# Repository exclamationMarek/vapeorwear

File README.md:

# VAPEorWEAR
Wearable SAO power pack

Designed around a battery, that is upcycled from a single use vape, that a friend of mine found (in worryingly large quantities) in the recycling room of his house. It features a proper battery charger and protection IC, so that the poor, abused lithium cell can now live a comfortable afterlife powering your shitty add ons!

# Features
* 400mAh upcycled battery that might smell like fruity vape juice
* Regulated 3.3V output, 1A max, with short circuit protection
* 2x M4 holes that should fit lanyard clips
* Rounded edges and no poking-out THT pins on the backside, to not ruin your nice t-shirt
* Battery protection and charging from USB
* On-Off switch (with a <3µA shutdown current)

# Kit content
If you received a kit, it should contain:
* 1x PCB
* 1x Up-cycled battery. It may smell fruity and be a bit sticky. I attempted to wash it.
* 3x Different ICs in SOT-23. Don't confuse which one is which!
* 1x USB connector
* 1x sliding switch
* 1x battery connector
* 1x SAO connector
* 1x 4.7uH inductor in 1008 package
* 1x 21k resistor
* 2x 1uF capacitor
* 3x 10uF capacitor
* 4x 560ohm resistor
* 5x 4.7k resistor

# Assembly instruction
For your convenience, most components are arranged in simple rows. The recommended order of soldering is row by row, and each row is listed **from left to right**

## ROW 1: LEDS
Negative (stripe) always faces left
1. White LED (charging indicator)
2. White LED (power indicator)

## ROW 2: LED resistors
1. 560R (sets brightness of charging LED)
2. 560R (sets brightness of power LED)
You can swap them for 4.7k ones if you want the LEDs dimmer

## ROW 3: ICs
Pin 1 (dot) is always bottom right
1. BRCL4054CME (battery charger). Package marking: "4054C"
2. MT3406 (buck converter). Package marking: "A1xx" (example: A15a)
3. RY2201 (battery protection). Package marking: "MKxxx" (example: MKJ3L)

## ROW 4: Capacitors
1. 1uF (bypass for charger)
2. 10uF (bypass for buck)
3. 10uF (output for buck)
4. 10uF (more output for buck, optional)
5. 1uF (bypass for protection IC)

## ROW 5: Resistors
1. 4.7k (charge current set resistor. 4.7k->212mA, 2k->500mA, 10k->100mA)
2. 4.7k (VOUT set resistor LOW)
3. 21k	(VOUT set resistor HIGH. Included combination results in 3.24V out)
4. 4.7k	(Buck converter ENABLE pull-up). Can be pretty much any value.
5. 560R	(Battery protection IC power filter)

## Remaining components:
Their position and orientation has been left as an exercise to the assembler
1. 4.7uH inductor for the buck converter
2. On-off switch
3. Battery connector
4. USB-C port
5. 2x 4.7k resistors near the USB-C port (yeah I know these are supposed to be 5.1k but I din't have those on a spool so this is what you get in the kit. Since it's a 1% one, It's stil in the 10% tollerance allowed for the 5.1k by the USB spec so as blasmphemous as this is, it should work)
6. SAO connector. Unkeyed, sorry!

# Post assembly test
1. Do not plug in battery yet!
2. Plug in USB power source and test if VBAT reads approx. 4.2V
	* The charge LED is allowed to blink erratically
3. Turn the switch ON and check if 3.3V out reads approx 3.3V 
4. Check polarity of battery cable. Compare it with the print on the silkscreen
5. If so, you can unplug the usb, plug in the battery and enjoy your VAPEorWEAR

# Design details
## [RY2201](https://www.lcsc.com/datasheet/C370889.pdf) battery protection IC
* Overcharge protection at 4.3V
* Overdischarge protection at 2.4V
* Overcurrent protection at 3.0A

## [BRCL4054CME](https://www.lcsc.com/datasheet/C305436.pdf) battery charger IC
* CCCV charging to 4.2V
* R11 sets charging current. Recommended 4.99k gives 200mA (2.5h charge time)
* For fastest allowed charging (500mA) use 2k resistor instead. 
* CHRG led will shine during charging, and gently glow when done

## [MT3406](https://www.lcsc.com/datasheet/C22462728.pdf) buck converter
* Efficiently produces 3.3V from VBAT
* 1A output continuous, 2A self-protected limit
* Paired with [INPAQ WIP252012P-4R7ML](https://www.lcsc.com/datasheet/C964123.pdf) inductor (4.7µH, 1.9A ISat, 196mΩ)
* Not a boost-buck, so output voltage will start dropping as VBAT drops below 3.4V

## [ON/OFF switch](https://www.lcsc.com/datasheet/C22435662.pdf) and PWR LED
* Switch controls the ENABLE pin of the buck converter
* LED is connected to the output 3.3V rail
* Quiescent current when OFF < 3µA
* Quiescent current when ON approx. 1.2mA, mostly due to the power LED

## [USB-C port](https://www.lcsc.com/datasheet/C42400650.pdf) for 5V input

## 31 x 13mm battery cavity
* With 4x 3x1.5mm zip-tie or tape slots for mounting
* Prominently shows the battery, no mechanical cell protection offered
* JST-ZH (1.5mm) 2-pin connector

## 2.54mm pin row for connecting to the SAO
* breaks out all SAO pins, and 5V and extra GND
* VCC, GND and I2C pins are arranged so that an I2C OLED (example SSD1306) can be connected directly, should the SAO feature a micro and wish to display something.

# Other notes
The component values are a bit funky, since they are heavily consolidated for making convinient kits. If you are assembling this with access to a full selection of passives, pick better values. The KiCad design files contain more recommended values.

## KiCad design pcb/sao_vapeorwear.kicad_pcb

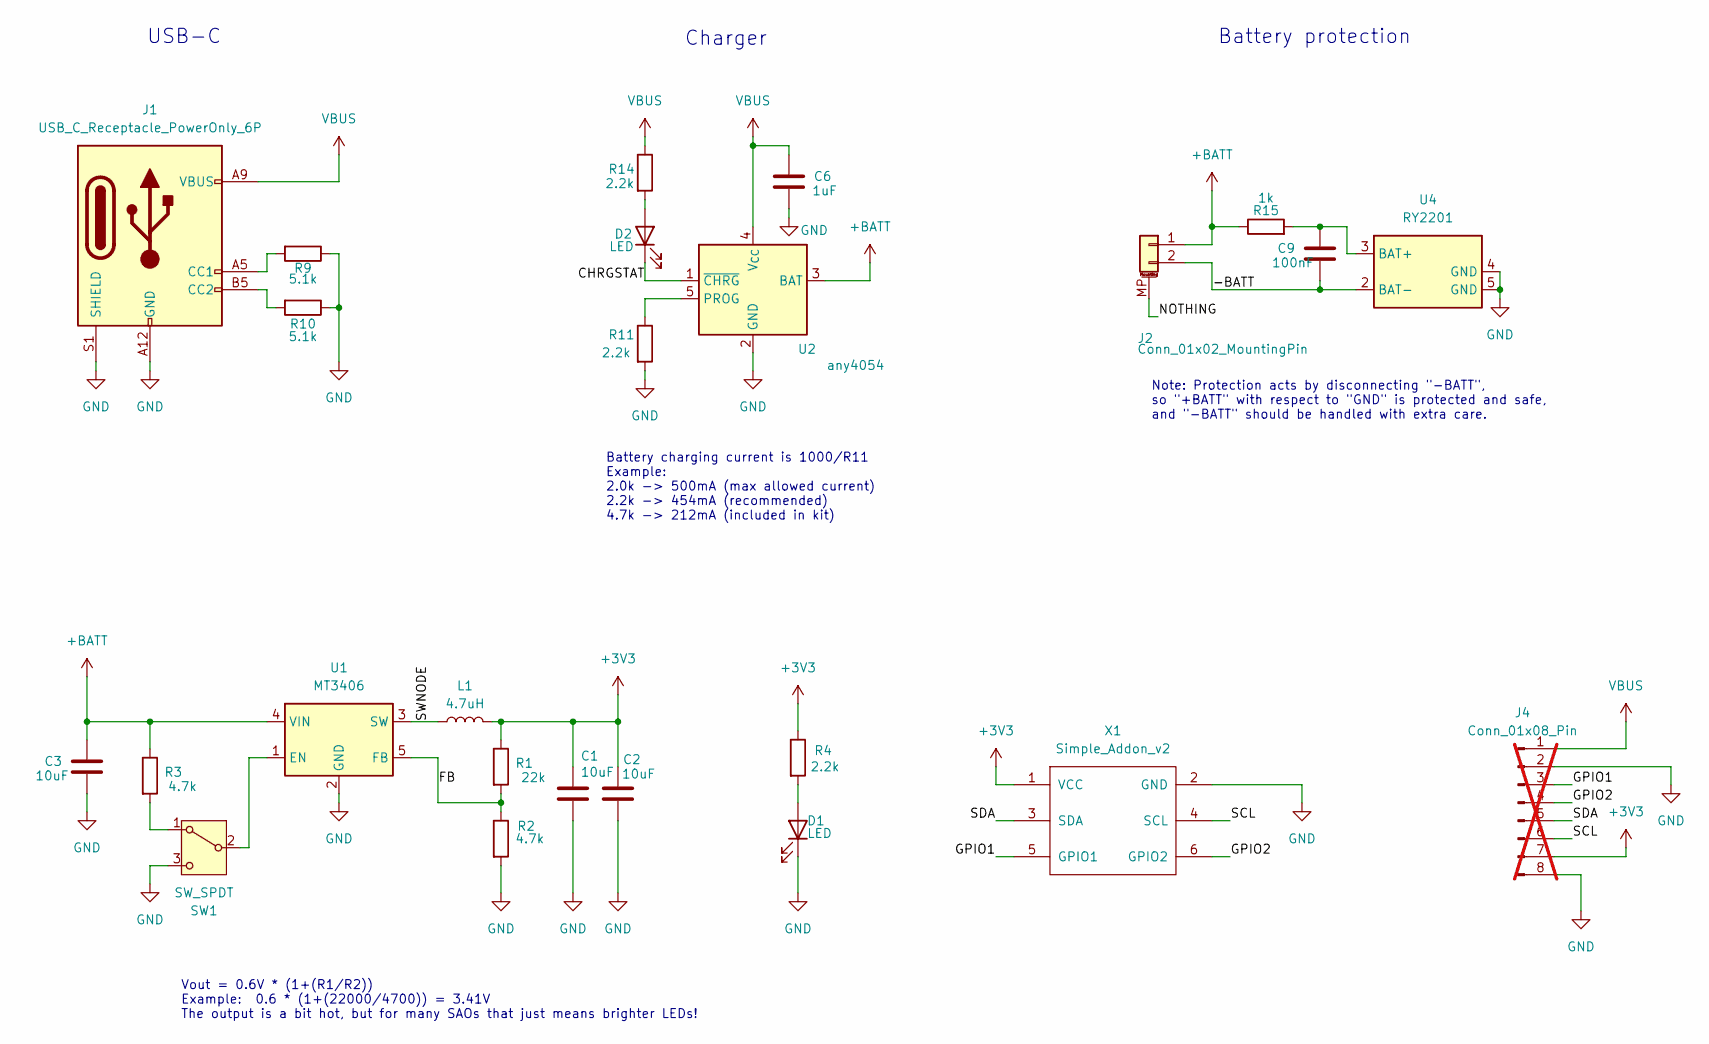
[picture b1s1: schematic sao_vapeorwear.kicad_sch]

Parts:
C1, C2, C3: 10uF; C_0603_1608Metric_Pad1.08x0.95mm_HandSolder
C6: 1uF; C_0603_1608Metric_Pad1.08x0.95mm_HandSolder
C9: 100nF; C_0603_1608Metric_Pad1.08x0.95mm_HandSolder
D1, D2: LED; LED_0603_1608Metric_Pad1.05x0.95mm_HandSolder
J1: USB_C_Receptacle_PowerOnly_6P; USB_C_Receptacle_GCT_USB4125-xx-x-0190_6P_TopMnt_Horizontal
J2: Conn_01x02_MountingPin; JST_ZH_S2B_1x02_HORIZONTAL
J4: Conn_01x08_Pin; PinHeader_1x08_P2.54mm_Vertical; not fitted
L1: 4.7uH; L_1008_2520Metric_Pad1.43x2.20mm_HandSolder
R1: 22k; R_0603_1608Metric_Pad0.98x0.95mm_HandSolder
R2, R3: 4.7k; R_0603_1608Metric_Pad0.98x0.95mm_HandSolder
R4, R11, R14: 2.2k; R_0603_1608Metric_Pad0.98x0.95mm_HandSolder
R9, R10: 5.1k; R_0603_1608Metric_Pad0.98x0.95mm_HandSolder
R15: 1k; R_0603_1608Metric_Pad0.98x0.95mm_HandSolder
SW1: SW_SPDT; SW_SPDT_PCM12
U1: MT3406; SOT-23-5_HandSoldering
U2: any4054; SOT-23-5_HandSoldering
U4: RY2201; SOT-23-5_HandSoldering
X1: Simple_Addon_v2; PinSocket_2x03_P2.54mm_Vertical_SMD

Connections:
+3V3: C1.1, C2.1, J4.7, L1.2, R1.1, R4.1, X1.1 (VCC)
+BATT: C3.1, J2.1, R3.1, R15.1, U1.4 (VIN), U2.3 (BAT)
/-BATT: C9.2, J2.2, U4.2 (BAT-)
/CHRGSTAT: D2.1 (K), U2.1 (~CHRG)
/FB: R1.2, R2.1, U1.5 (FB)
/GPIO1: J4.3, X1.5 (GPIO1)
/GPIO2: J4.4, X1.6 (GPIO2)
/NOTHING: J2.MP (MountPin)
/SCL: J4.6, X1.4 (SCL)
/SDA: J4.5, X1.3 (SDA)
/SWNODE: L1.1, U1.3 (SW)
GND: C1.2, C2.2, C3.2, C6.2, D1.1 (K), J1.A12 (GND), J1.B12 (GND), J1.S1 (SHIELD), J4.2, J4.8, R2.2, R9.1, R10.1, R11.2, SW1.3 (C), U1.2 (GND), U2.2 (GND), U4.4 (GND), U4.5 (GND), X1.2 (GND)
unnamed: D1.2 (A), R4.2
unnamed: D2.2 (A), R14.2
unnamed: J1.A5 (CC1), R9.2
unnamed: J1.B5 (CC2), R10.2
unnamed: R3.2, SW1.1 (A)
unnamed: SW1.2 (B), U1.1 (EN)
unnamed: R11.1, U2.5 (PROG)
unnamed: C9.1, R15.2, U4.3 (BAT+)
VBUS: C6.1, J1.A9 (VBUS), J1.B9 (VBUS), J4.1, R14.1, U2.4 (V_{CC})

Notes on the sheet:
Charger
Battery protection
Vout = 0.6V * (1+(R1/R2)) Example: 0.6 * (1+(22000/4700)) = 3.41V The output is a bit hot, but for many SAOs that just means brighter LEDs!
Battery charging current is 1000/R11 Example: 2.0k -> 500mA (max allowed current) 2.2k -> 454mA (recommended) 4.7k -> 212mA (included in kit)
USB-C
Note: Protection acts by disconnecting "-BATT", so "+BATT" with respect to "GND" is protected and safe, and "-BATT" should be handled with extra care.

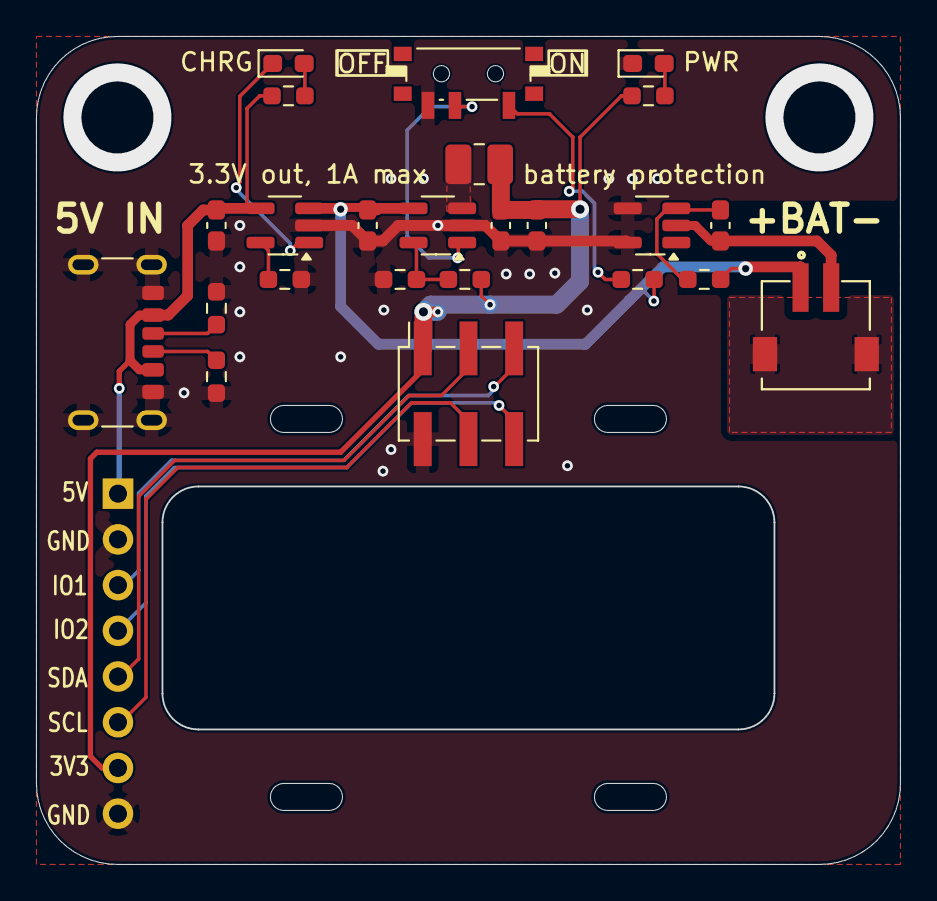
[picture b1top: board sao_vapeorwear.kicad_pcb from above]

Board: 2 copper layers, 48.0 x 46.0 mm, 25 parts (0 on the bottom side), 20 nets.

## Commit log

2026-04-29 made the documentation a bit more tldr resistant
2026-05-17 Better documentation
2026-05-25 component values
